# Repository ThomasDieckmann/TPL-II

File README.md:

# TPL-II
## Taupunktlüftung II => dewpoint ventilation II
Description in progress....

The original project Taupunktlüftung is created by ct/Heise.

I extended and modified the code for some additional functions and some optional hardware has been added, too.

## purpose, just in case, you don't know...

## Hardware-Overview

the project hardware is based on some separate modules.
1. mainboard
2. power supply
3. relais board
4. I2C display

### the mainboard
the mainboard is developed by myself using KiCAD software. it has sockets for the Arduino nano, which is obligatory and for an ESP01 or Wemos D1. the source code published here is developed with Arduino IDE and has to be uploaded to the Atmega 328P chip with new bootloader. you can add an ESP8266 (wemos D1 mini pro or ESP01) to this system. this additional module is intendet to be programmed with Tasmota firmware. It reads serial data from the Arduino board an can deliver the data to an MQTT server. With serialsend you can use the ESP chip, so send serial data to the Arduino, for example, to initiate a button press.

### power supply

Switching power supply, board creaded with KiCAD. Output is 5V 10W (or more).

### relais board

2 relais baord from a chinese manufacturer. be sure to buy good quality with air gap between the contacts.

### I2C display

LCD background lit text display with 2 x 40 characters HD44780 compatible and I2C interface

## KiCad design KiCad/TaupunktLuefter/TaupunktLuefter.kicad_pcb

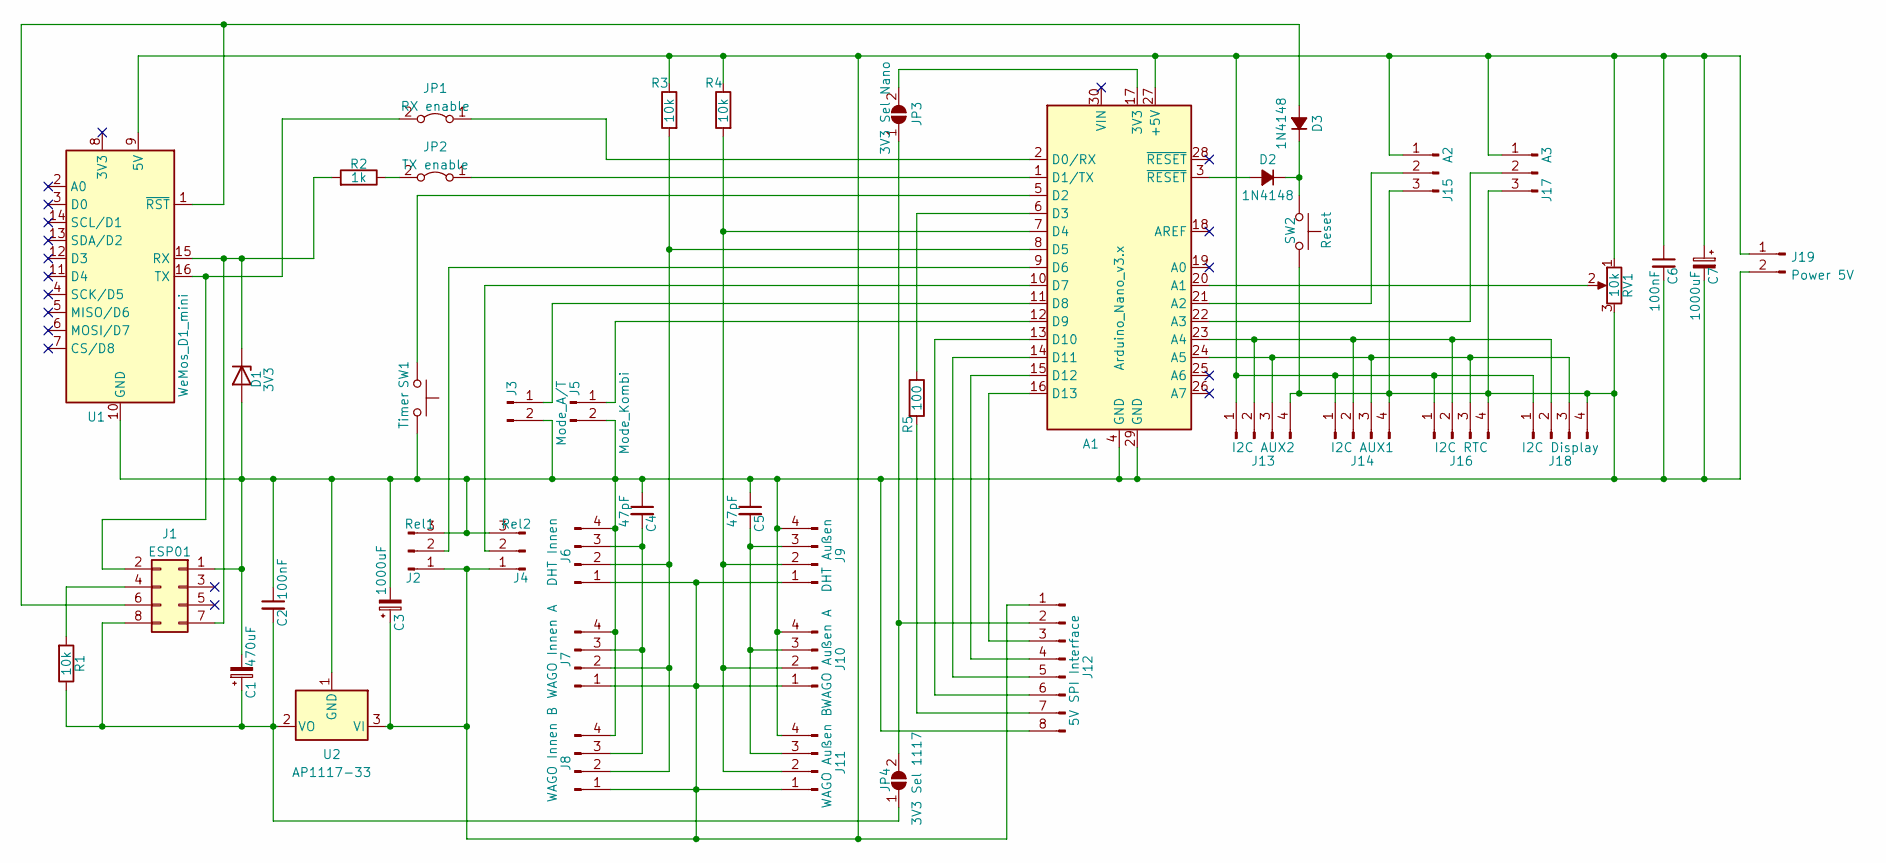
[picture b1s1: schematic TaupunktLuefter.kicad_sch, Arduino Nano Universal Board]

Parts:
A1: Arduino_Nano_v3.x; Arduino_Nano
C1: 470uF; CP_Radial_D10.0mm_P5.00mm
C2, C6: 100nF; C_Rect_L7.0mm_W2.0mm_P5.00mm
C3, C7: 1000uF; CP_Radial_D12.5mm_P7.50mm
C4, C5: 47pF; C_Rect_L7.0mm_W2.0mm_P5.00mm
D1: 3V3; D_A-405_P2.54mm_Vertical_KathodeUp
D2, D3: 1N4148; D_A-405_P2.54mm_Vertical_KathodeUp
J1: ESP01; PinSocket_2x04_P2.54mm_Vertical
J2: Rel1; PinHeader_1x03_P2.54mm_Vertical
J3: Mode_A/T; PinHeader_1x02_P2.54mm_Vertical
J4: Rel2; PinHeader_1x03_P2.54mm_Vertical
J5: Mode_Kombi; PinHeader_1x02_P2.54mm_Vertical
J6: DHT Innen; PinHeader_1x04_P2.54mm_Vertical
J7: WAGO Innen A; PinHeader_1x04_P2.54mm_Vertical
J8: WAGO Innen B; PinHeader_1x04_P2.54mm_Vertical
J9: DHT Außen; PinHeader_1x04_P2.54mm_Vertical
J10: WAGO Außen A; PinHeader_1x04_P2.54mm_Vertical
J11: WAGO Außen B; PinHeader_1x04_P2.54mm_Vertical
J12: 5V SPI Interface; PinHeader_1x08_P2.54mm_Vertical
J13: I2C AUX2; PinHeader_1x04_P2.54mm_Vertical
J14: I2C AUX1; PinHeader_1x04_P2.54mm_Vertical
J15: A2; PinHeader_1x03_P2.54mm_Vertical
J16: I2C RTC; PinHeader_1x04_P2.54mm_Vertical
J17: A3; PinHeader_1x03_P2.54mm_Vertical
J18: I2C Display; PinHeader_1x04_P2.54mm_Vertical
J19: Power 5V; Molex_KK-254_AE-6410-02A_1x02_P2.54mm_Vertical
JP1: RX enable; PinHeader_1x02_P2.54mm_Vertical
JP2: TX enable; PinHeader_1x02_P2.54mm_Vertical
JP3: 3V3 Sel Nano; SolderJumper-2_P1.3mm_Open_Pad1.0x1.5mm
JP4: 3V3 Sel 1117; SolderJumper-2_P1.3mm_Open_Pad1.0x1.5mm
R1, R3, R4: 10k; R_Axial_DIN0207_L6.3mm_D2.5mm_P2.54mm_Vertical
R2: 1k; R_Axial_DIN0207_L6.3mm_D2.5mm_P2.54mm_Vertical
R5: 100; R_Axial_DIN0207_L6.3mm_D2.5mm_P2.54mm_Vertical
RV1: 10k; PinHeader_1x03_P2.54mm_Vertical
SW1: Timer; PinHeader_1x02_P2.54mm_Vertical
SW2: Reset; PinHeader_1x02_P2.54mm_Vertical
U1: WeMos_D1_mini; WEMOS_D1_mini_light
U2: AP1117-33; SOT-223-3_TabPin2

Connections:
unnamed: A1.1 (D1/TX), JP2.1 (A)
unnamed: A1.2 (D0/RX), JP1.1 (A)
unnamed: A1.3 (~RESET), D2.2 (A)
unnamed: A1.5 (D2), SW1.1
unnamed: A1.6 (D3), R5.1
unnamed: A1.7 (D4), J9.2, J10.2, J11.2, R4.2
unnamed: A1.8 (D5), J6.2, J7.2, J8.2, R3.2
unnamed: A1.9 (D6), J2.2
unnamed: A1.10 (D7), J4.2
unnamed: A1.11 (D8), J3.1
unnamed: A1.12 (D9), J5.1
unnamed: A1.13 (D10), J12.6
unnamed: A1.14 (D11), J12.5
unnamed: A1.15 (D12), J12.4
unnamed: A1.16 (D13), J12.3
unnamed: A1.17 (3V3), JP3.2 (B)
unnamed: A1.20 (A1), RV1.2
unnamed: A1.21 (A2), J15.2
unnamed: A1.22 (A3), J17.2
unnamed: A1.23 (A4), J13.2, J14.2, J16.2, J18.2
unnamed: A1.24 (A5), J13.3, J14.3, J16.3, J18.3
unnamed: A1.27 (+5V), C3.1, C6.1, C7.1, J2.1, J4.1, J6.1, J7.1, J8.1, J9.1, J10.1, J11.1, J12.1, J13.1, J14.1, J15.1, J16.1, J17.1, J18.1, J19.1, R3.1, R4.1, RV1.1, U1.9 (5V), U2.3 (VI)
unnamed: A1.4 (GND), A1.29 (GND), C1.2, C2.1, C3.2, C4.1, C5.1, C6.2, C7.2, D1.2 (A), J1.1, J2.3, J3.2, J4.3, J5.2, J6.4, J7.4, J8.4, J9.4, J10.4, J11.4, J12.8, J13.4, J14.4, J15.3, J16.4, J17.3, J18.4, J19.2, RV1.3, SW1.2, SW2.2, U1.10 (GND), U2.1 (GND)
unnamed: C1.1, C2.2, J1.8, JP4.1 (A), R1.1, U2.2 (VO)
unnamed: C4.2, J6.3, J7.3, J8.3
unnamed: C5.2, J9.3, J10.3, J11.3
unnamed: D2.1 (K), D3.1 (K), SW2.1
unnamed: D3.2 (A), J1.6, U1.1 (~RST)
unnamed: J1.2, JP1.2 (B), U1.16 (TX)
unnamed: J1.4, R1.2
unnamed: D1.1 (K), J1.7, R2.2, U1.15 (RX)
unnamed: J12.2, JP3.1 (A), JP4.2 (B)
unnamed: J12.7, R5.2
unnamed: JP2.2 (B), R2.1

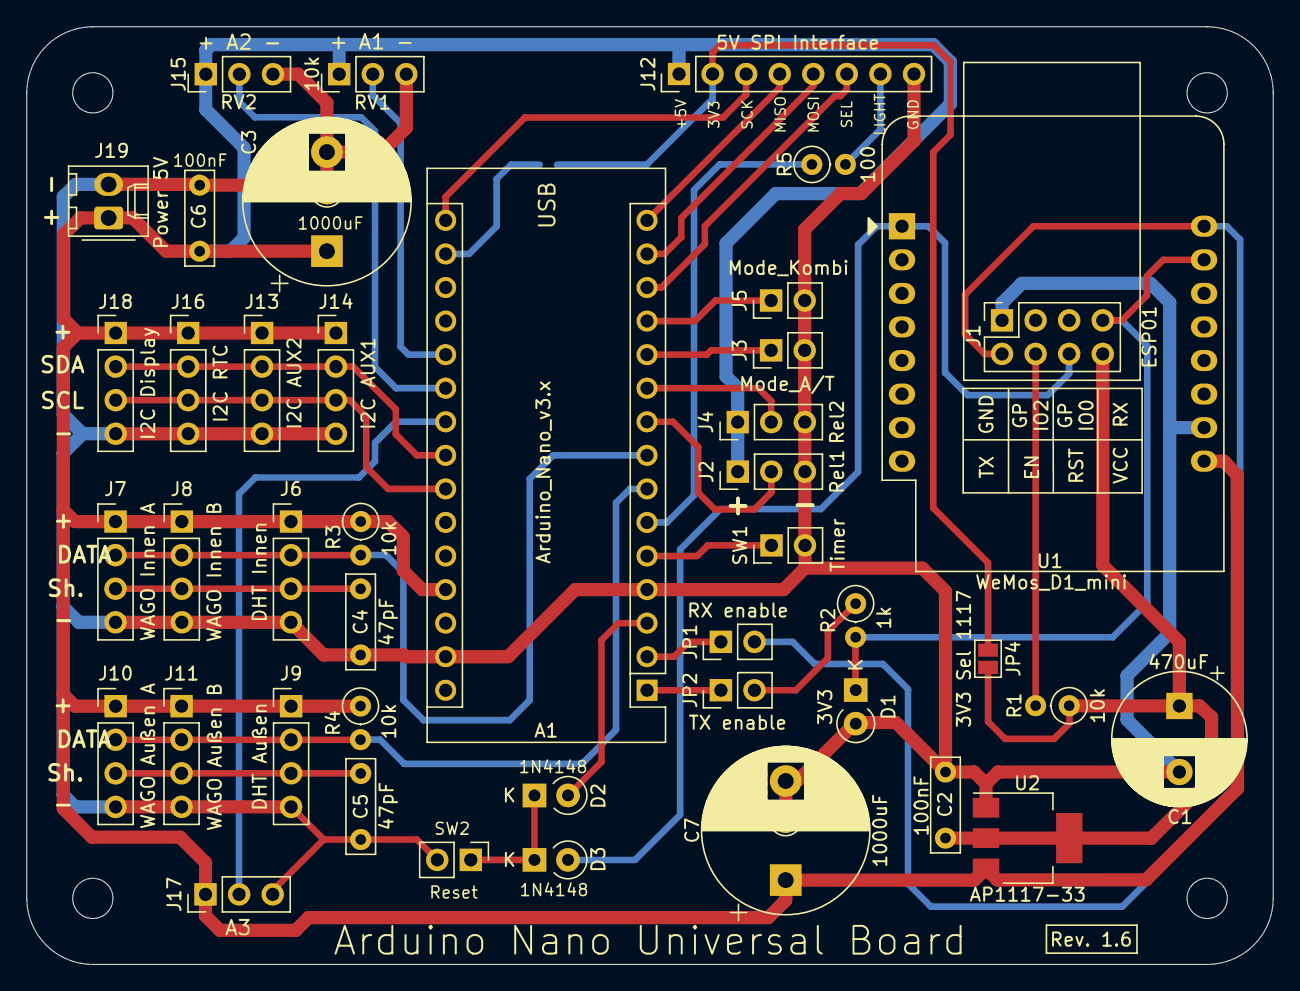
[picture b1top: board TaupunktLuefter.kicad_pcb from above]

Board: 2 copper layers, 94.3 x 71.0 mm, 44 parts (1 on the bottom side), 34 nets.

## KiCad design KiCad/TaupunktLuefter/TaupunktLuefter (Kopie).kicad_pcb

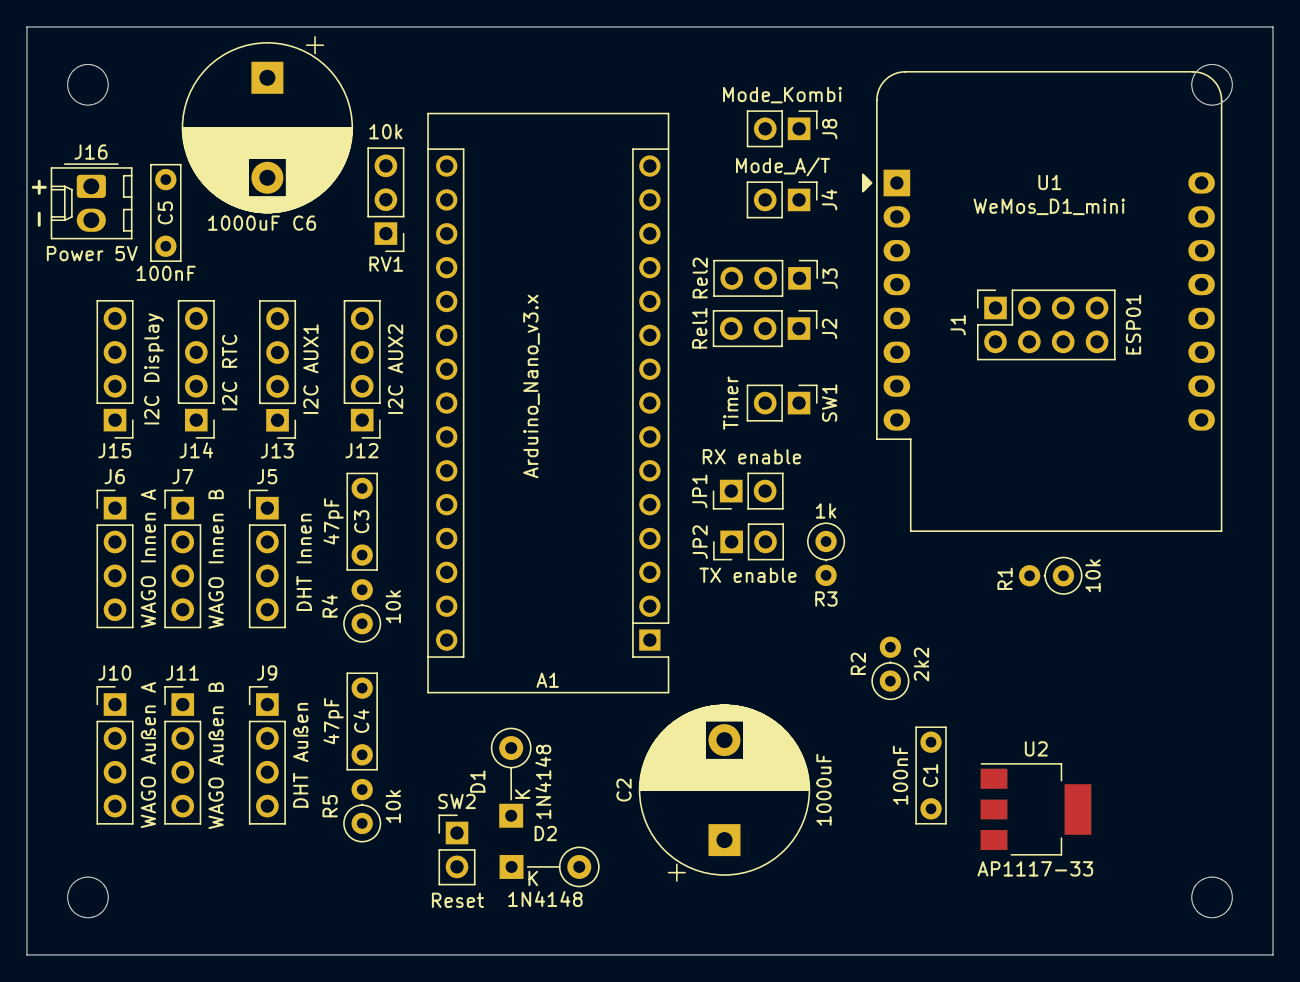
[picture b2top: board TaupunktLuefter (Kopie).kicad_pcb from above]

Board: 2 copper layers, 93.5 x 69.6 mm, 37 parts (0 on the bottom side), 25 nets, no tracks yet.

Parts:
A1: Arduino_Nano_v3.x; Arduino_Nano
C1, C5: 100nF; C_Rect_L7.0mm_W2.0mm_P5.00mm
C2, C6: 1000uF; CP_Radial_D12.5mm_P7.50mm
C3, C4: 47pF; C_Rect_L7.0mm_W2.0mm_P5.00mm
D1, D2: 1N4148; D_A-405_P5.08mm_Vertical_KathodeUp
J1: ESP01; PinSocket_2x04_P2.54mm_Vertical
J2: Rel1; PinHeader_1x03_P2.54mm_Vertical
J3: Rel2; PinHeader_1x03_P2.54mm_Vertical
J4: Mode_A/T; PinHeader_1x02_P2.54mm_Vertical
J5: DHT Innen; PinHeader_1x04_P2.54mm_Vertical
J6: WAGO Innen A; PinHeader_1x04_P2.54mm_Vertical
J7: WAGO Innen B; PinHeader_1x04_P2.54mm_Vertical
J8: Mode_Kombi; PinHeader_1x02_P2.54mm_Vertical
J9: DHT Außen; PinHeader_1x04_P2.54mm_Vertical
J10: WAGO Außen A; PinHeader_1x04_P2.54mm_Vertical
J11: WAGO Außen B; PinHeader_1x04_P2.54mm_Vertical
J12: I2C AUX2; PinHeader_1x04_P2.54mm_Vertical
J13: I2C AUX1; PinHeader_1x04_P2.54mm_Vertical
J14: I2C RTC; PinHeader_1x04_P2.54mm_Vertical
J15: I2C Display; PinHeader_1x04_P2.54mm_Vertical
J16: Power 5V; Molex_KK-254_AE-6410-02A_1x02_P2.54mm_Vertical
JP1: RX enable; PinHeader_1x02_P2.54mm_Vertical
JP2: TX enable; PinHeader_1x02_P2.54mm_Vertical
R1, R4, R5: 10k; R_Axial_DIN0207_L6.3mm_D2.5mm_P2.54mm_Vertical
R2: 2k2; R_Axial_DIN0207_L6.3mm_D2.5mm_P2.54mm_Vertical
R3: 1k; R_Axial_DIN0207_L6.3mm_D2.5mm_P2.54mm_Vertical
RV1: 10k; PinHeader_1x03_P2.54mm_Vertical
SW1: Timer; PinHeader_1x02_P2.54mm_Vertical
SW2: Reset; PinHeader_1x02_P2.54mm_Vertical
U1: WeMos_D1_mini; WEMOS_D1_mini_light
U2: AP1117-33; SOT-223-3_TabPin2

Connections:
unnamed: A1.1 (D1/TX), JP2.1 (A)
unnamed: A1.2 (D0/RX), JP1.1 (A)
unnamed: A1.5 (D2), SW1.2
unnamed: A1.7 (D4), J9.3, J10.3, J11.3, R5.2
unnamed: A1.8 (D5), J5.3, J6.3, J7.3, R4.2
unnamed: A1.9 (D6), J2.2
unnamed: A1.10 (D7), J3.2
unnamed: A1.11 (D8), J4.2
unnamed: A1.20 (A1), RV1.2
unnamed: A1.23 (A4), J12.3, J13.3, J14.3, J15.3
unnamed: A1.24 (A5), J12.2, J13.2, J14.2, J15.2
unnamed: A1.27 (+5V), C5.1, C6.1, J5.4, J6.4, J7.4, J9.4, J10.4, J11.4, J12.4, J13.4, J14.4, J15.4, J16.1, R4.1, R5.1, RV1.1, U1.9 (5V)
unnamed: A1.28 (~RESET), D1.2 (A)
unnamed: C1.2, J1.8, R1.1, U2.2 (VO)
unnamed: C2.1, J2.3, J3.3, U2.3 (VI)
unnamed: C3.2, J5.2, J6.2, J7.2
unnamed: C4.2, J9.2, J10.2, J11.2
unnamed: D1.1 (K), D2.1 (K), SW2.2
unnamed: D2.2 (A), J1.6, U1.1 (~RST)
unnamed: A1.4 (GND), A1.29 (GND), C1.1, C2.2, C3.1, C4.1, C5.2, C6.2, J1.1, J2.1, J3.1, J4.1, J5.1, J6.1, J7.1, J8.1, J9.1, J10.1, J11.1, J12.1, J13.1, J14.1, J15.1, J16.2, R2.1, RV1.3, SW1.1, SW2.1, U1.10 (GND), U2.1 (GND)
unnamed: J1.2, JP1.2 (B), U1.16 (TX)
unnamed: J1.4, R1.2
unnamed: A1.12 (D9), J8.2
unnamed: JP2.2 (B), R3.1
unnamed: J1.7, R2.2, R3.2, U1.15 (RX)

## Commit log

2025-02-22 Create mt
2025-02-22 several photos
    will rename/describe them later
2025-02-25 Create GPL LICENSE
